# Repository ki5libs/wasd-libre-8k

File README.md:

View this project on [CADLAB.io](https://cadlab.io/project/23397). 

# WASD-libre-8K

FPGA-based keyboard controller

## Goal Features
 - open-source firmware and toolchain
 - QMK-compatibility (patches are planning)
 - WASD-keyboard compatibility
 - Mechanical compatibility with existing popular 80% keyboards (i.e XD87 from KRepublic)
 - controlling keyboard backlight
 - controlling keyboard RGB-highlight
 - I2C (ready) and USB (planning) interfaces
 
 The work is in progress...

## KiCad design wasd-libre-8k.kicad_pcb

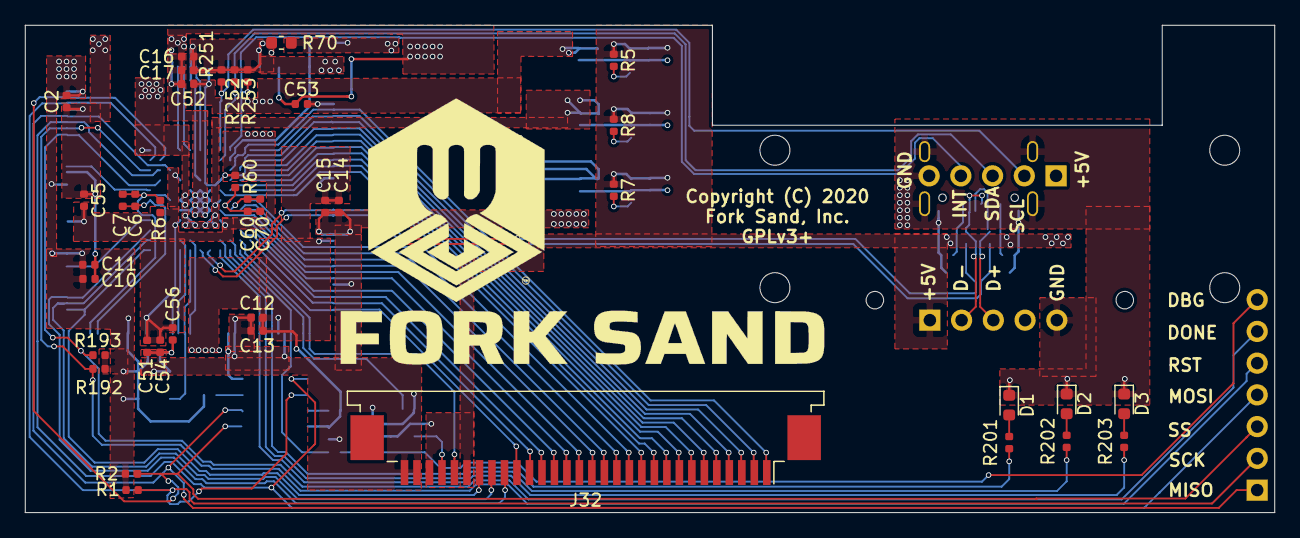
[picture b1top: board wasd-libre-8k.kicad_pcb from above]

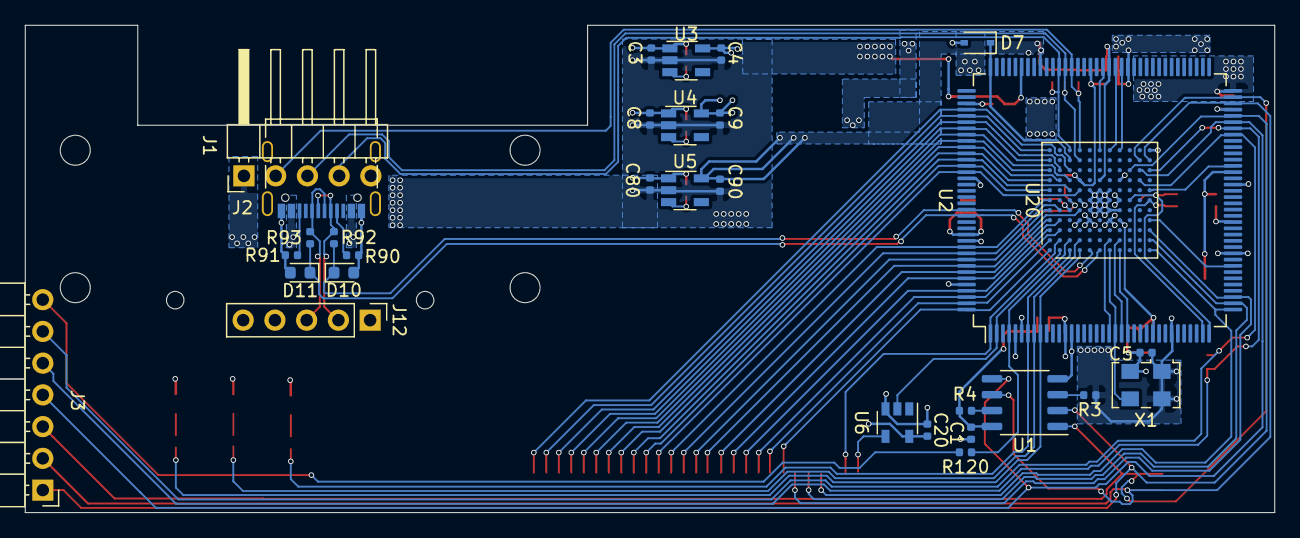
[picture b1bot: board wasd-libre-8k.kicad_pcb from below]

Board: 2 copper layers, 100.0 x 39.0 mm, 70 parts (31 on the bottom side), 74 nets.

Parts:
C1, C2, C5, C6, C10, C11, C12, C13, C14, C15, C16, C17, C20, C52, C53, C54, C55, C60: 0.1 uF; C_0402_1005Metric
C3, C4, C8, C9, C80, C90: 1 uF; C_0402_1005Metric
C7, C51, C70: 10 uF; C_0402_1005Metric
C56: 0.01 uF; C_0402_1005Metric
D1, D2, D3: TO-1608BC-MYF; D_0603_1608Metric
D7: 1PS76SB10; D_SOD-323
D10, D11: PGB1010603NRHF; D_0603_1608Metric
J1: Conn_01x05; PinHeader_1x05_P2.54mm_Horizontal
J2: USB_C_Receptacle_USB2.0; USB_C_Receptacle_Palconn_UTC16-G
J3: Conn_01x07; PinHeader_1x07_P2.54mm_Horizontal
J12: Conn_01x05; PinHeader_1x05_P2.54mm_Vertical
J32: Conn_01x30; TE_3-84953-0_1x30-1MP_P1.0mm_Horizontal
R1, R2, R3, R4, R5, R7, R8, R192, R193, R251, R252, R253: 10K; R_0402_1005Metric
R6, R60: 100; R_0402_1005Metric
R70: 0; R_0603_1608Metric
R90, R91: 5K1; R_0402_1005Metric
R92, R93: 22; R_0402_1005Metric
R120: 300; R_0402_1005Metric
R201, R202, R203: 200; R_0402_1005Metric
U1: MX25R3235FM1xx1; SOP-8_3.9x4.9mm_P1.27mm
U2: ICE40HX1K-TQ144; TQFP-144_20x20mm_P0.5mm
U3: NCV8114ASN120T1G; TSOT-23-5
U4: NCV8114ASN330T1G; TSOT-23-5
U5: NCV8114ASN180T1G; TSOT-23-5
U6: SN74LVC1G14DBV; SOT-23-5
U20: ICE40HX8K-BG121; BGA-121_9.0x9.0mm_Layout11x11_P0.8mm_Ball0.4mm_Pad0.35mm_NS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
X1: XO53, 12 MHz; Oscillator_SMD_EuroQuartz_XO53-4Pin_5.0x3.2mm

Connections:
+1V2: C4.2, C51.2, C52.2, C53.2, C54.2, C55.2, C56.2, R6.1, R60.1, U2.27, U2.51, U2.92, U2.111, U3.5, U20.D4, U20.D8, U20.H4, U20.H8
+3V3: C1.2, C2.2, C5.2, C9.2, C10.2, C11.2, C12.2, C13.2, C14.2, C15.2, D7.2, R1.1, R2.1, R3.1, R4.1, R70.2, R192.2, R193.2, U1.8, U2.6, U2.30, U2.46, U2.57, U2.72, U2.123, U2.133, U4.5, U20.D6, U20.E4, U20.G4, U20.H6, U20.L11, X1.1, X1.4
+5V: C3.2, C8.2, C20.2, C80.2, J1.1, J2.A4, J2.A9, J2.B4, J2.B9, J12.1, J32.25, J32.28, R5.1, R7.1, R8.1, U3.1, U4.1, U5.1, U6.5
+VSW: C16.2, C17.2, C90.2, R70.1, R251.1, R252.1, R253.1, U2.89, U2.100, U5.5, U20.F8
/CLK: U2.21, U20.G1, X1.3
/COL0: J32.17, U2.139, U20.B4
/COL1: J32.18, U2.141, U20.A3
/COL2: J32.19, U2.142, U20.B3
/COL3: J32.20, U2.143, U20.A2
/COL4: J32.21, U2.144, U20.A1
/COL5: J32.22, U2.39, U20.L3
/COL6: J32.23, U2.38, U20.L2
/COL7: J32.24, U2.37, U20.L1
/D+: J2.A6, J2.B6, J12.3, R93.2
/D-: J2.A7, J2.B7, J12.2, R92.2
/DEBUG: R120.1, U2.4, U20.C2
/DEBUG_LED1: R201.1, U2.7, U20.C1
/DEBUG_LED2: R202.1, U2.8, U20.D2
/DEBUG_LED3: R203.1, U2.9, U20.D1
/DEBUG_TX: J3.7, R120.2
/GNDPLL0: C6.1, C7.1, U2.35, U20.L6
/I2C0_SCL: J1.2, R251.2, U2.95, U20.D11
/I2C0_SDA: J1.3, R252.2, U2.96, U20.D10
/ICE_CDONE: J3.6, R193.1, U2.65, U20.K8
/ICE_CRST_B: J3.5, R192.1, U2.66, U20.L9
/ICE_MISO: J3.1, U1.2, U2.68, U20.J9
/ICE_MOSI: J3.4, U1.5, U2.67, U20.K9
/ICE_SCK: J3.2, R1.2, U1.6, U2.70, U20.L10
/ICE_SS: J3.3, R2.2, U1.1, U2.71, U20.K10
/INTERRUPT: J1.4, R253.2, U2.97, U20.C11
/PWM_OUT: J32.26, U2.1, U20.B2
/RGB_DRV: U2.2, U6.2, U20.B1
/RGB_OUT: J32.27, U6.4
/ROW0: J32.1, U2.112, U20.C9
/ROW1: J32.2, U2.113, U20.A11
/ROW2: J32.3, U2.114, U20.B9
/ROW3: J32.4, U2.115, U20.A10
/ROW4: J32.5, U2.116, U20.C8
/ROW5: J32.6, U2.117, U20.A9
/ROW6: J32.7, U2.118, U20.B8
/ROW7: J32.8, U2.119, U20.A8
/ROW8: J32.9, U2.120, U20.C7
/ROW9: J32.10, U2.121, U20.A7
/ROW10: J32.11, U2.122, U20.D7
/ROW11: J32.12, U2.134, U20.A6
/ROW12: J32.13, U2.135, U20.B5
/ROW13: J32.14, U2.136, U20.A5
/ROW14: J32.15, U2.137, U20.D5
/ROW15: J32.16, U2.138, U20.A4
/SPR1: U2.23, U20.H1
/SPR2: U2.22, U20.H2
/SPR3: U2.20, U20.G2
/SPR4: U2.44, U20.L4
/SPR5: U2.60, U20.L7
/SPR6: U2.87, U20.H11
/SPR7: U2.88, U20.G11
/SPR8: U2.90, U20.F11
/USB_D+: D11.1, R93.1, U2.129, U20.F1
/USB_D-: D10.1, R92.1, U2.128, U20.E1
/VCCPLL0: C6.2, C7.2, R6.2, U2.36, U20.J6
/VPP_2V5: D7.1, U2.108, U20.C10
GND: C1.1, C2.1, C3.1, C4.1, C5.1, C8.1, C9.1, C10.1, C11.1, C12.1, C13.1, C14.1, C15.1, C16.1, C17.1, C20.1, C51.1, C52.1, C53.1, C54.1, C55.1, C56.1, C80.1, C90.1, D1.1, D2.1, D3.1, D10.2, D11.2, J1.5, J2.A1, J2.A12, J2.B1, J2.B12, J2.S1, J12.5, J32.29, J32.30, R90.1, R91.1, U1.4, U2.5, U2.13, U2.14, U2.59, U2.69, U2.86, U2.103, U2.132, U2.140, U3.2, U4.2, U5.2, U6.3, U20.E5, U20.E6, U20.E7, U20.F5, U20.F6, U20.F7, U20.G5, U20.G6, U20.G7, U20.H5, X1.2
unnamed: C60.1, C70.1, U20.C5
unnamed: C60.2, C70.2, R60.2, U20.C6
unnamed: D1.2, R201.2
unnamed: D2.2, R202.2
unnamed: D3.2, R203.2
unnamed: J2.A5, R90.2
unnamed: J2.B5, R91.2
unnamed: R3.2, U1.3
unnamed: R4.2, U1.7
unnamed: R5.2, U3.3
unnamed: R7.2, U5.3
unnamed: R8.2, U4.3

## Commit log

2020-01-11 Test version production
2020-01-26 Some USB changes
2020-01-26 Fix mechanical dimensions, adding spare lines
2020-01-27 Silkscreen sign for prog port
2020-02-05 RGB LED level converter added
2020-02-12 J32 (32 pins) replaced by 30 pins for using TE connector
2020-02-20 Adding some silkscreen, moved I2C lines, added additional holes for USB
2020-02-21 Old FPC connector removed
2020-02-21 Reworked for production cost decrease
2020-02-24 Renderings
2020-02-24 README
2020-10-13 Backlink to CADLAB.io has been added.

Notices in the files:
wasd-libre-8k.kicad_pcb:
Copyright (C) 2020
GPLv3+
